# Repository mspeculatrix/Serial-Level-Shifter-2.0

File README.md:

# Serial level shifter

This was always intended just as a daughterboard for my SmartParallel serial-to-parrallel printer interface card. It translates the 5V logic levels on the SmartParallel to 3.3V signals more suited for devices such as the Raspberry Pi.

**However**, experiments have shown that the TXB0104 chip used to do the level shifting can have severely limited power when it comes to driving the signal lines. As a result, this board might have very restricted applications.

Main description and explanation of the board:  https://mansfield-devine.com/speculatrix/2019/06/ttl-serial-level-shifter/
Details of problems encountered: https://mansfield-devine.com/speculatrix/2019/07/smartparallel-serial-shifter-issues/

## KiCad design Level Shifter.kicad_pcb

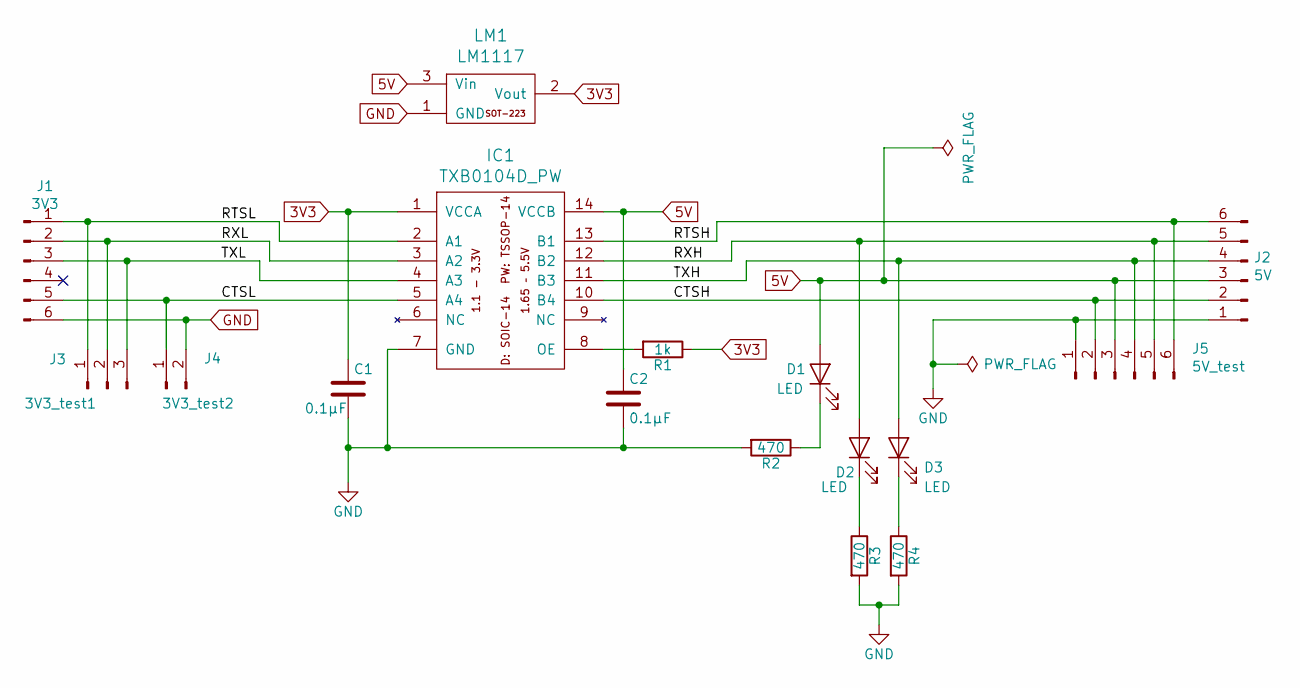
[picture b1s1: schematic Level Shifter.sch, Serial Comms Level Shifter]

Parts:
C1, C2: 0.1µF; C_1206
D1, D2, D3: LED; LED_1206
IC1: TXB0104D_PW; SOIC-14_3.9x8.7mm_Pitch1.27mm
J1: 3V3; Pin_Header_Straight_1x06
J2: 5V; Pin_Header_Straight_1x06
J3: 3V3_test1; Pin_Header_Straight_1x03
J4: 3V3_test2; Pin_Header_Straight_1x02
J5: 5V_test; Pin_Header_Straight_1x06
LM1: LM1117; SOT-223
R1: 1k; R_1206
R2, R3, R4: 470; R_1206

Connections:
3V3: C1.1, IC1.1 (VCCA), LM1.2 (Vout), R1.1
5V: C2.1, D1.2 (A), IC1.14 (VCCB), J2.3, J5.3, LM1.3 (Vin)
/CTSH: IC1.10 (B4), J2.2, J5.2
/CTSL: IC1.5 (A4), J1.5, J4.1
/RTSH: IC1.13 (B1), J2.6, J5.6
/RTSL: IC1.2 (A1), J1.1, J3.1
/RXH: D2.2 (A), IC1.12 (B2), J2.5, J5.5
/RXL: IC1.3 (A2), J1.2, J3.2
/TXH: D3.2 (A), IC1.11 (B3), J2.4, J5.4
/TXL: IC1.4 (A3), J1.3, J3.3
GND: C1.2, C2.2, IC1.7 (GND), J1.6, J2.1, J4.2, J5.1, LM1.1 (GND), R2.2, R3.2, R4.2
unnamed: D1.1 (K), R2.1
unnamed: D2.1 (K), R3.1
unnamed: D3.1 (K), R4.1
unnamed: IC1.8 (OE), R1.2

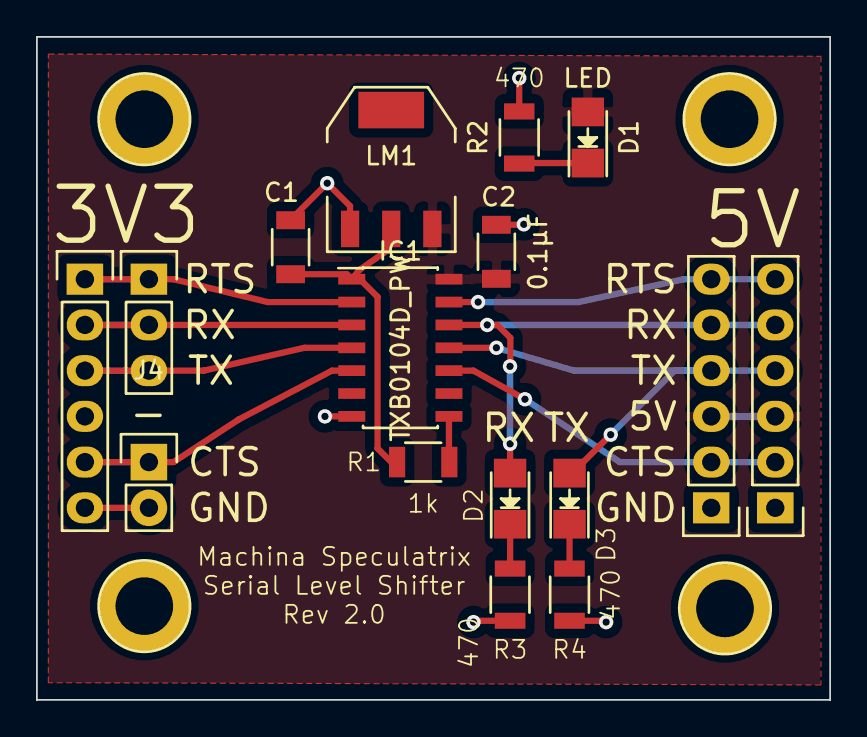
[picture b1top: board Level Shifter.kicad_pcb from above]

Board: 2 copper layers, 44.1 x 36.8 mm, 16 parts (0 on the bottom side), 15 nets.

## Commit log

2019-06-18 Gerbers tidied up
2019-07-22 Revised with fixes
